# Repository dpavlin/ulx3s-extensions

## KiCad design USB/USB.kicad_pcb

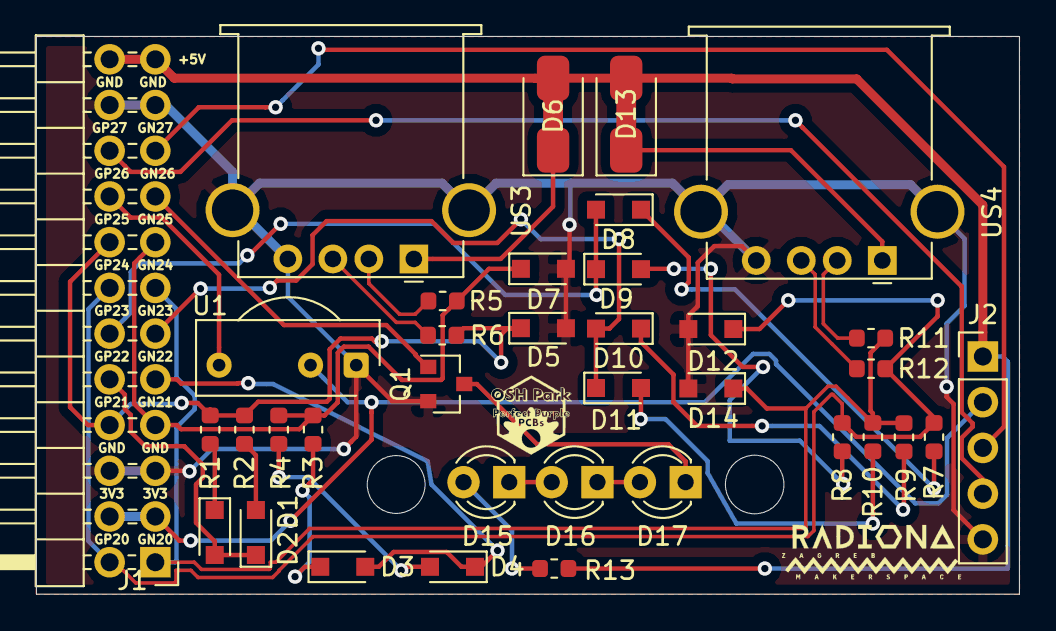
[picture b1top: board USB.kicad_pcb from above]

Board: 2 copper layers, 54.6 x 31.0 mm, 36 parts (0 on the bottom side), 33 nets.

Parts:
D1, D2, D3, D4, D8, D9, D10, D11: 1N914; D_SOD-323_HandSoldering
D5, D7, D12, D14: 3.6V; D_SOD-323_HandSoldering
D6, D13: 0; D_SMA_Jumper_NC
D15, D16, D17: LED; LED_D3.0mm_IRBlack
J1: Conn_02x12_Odd_Even; PinHeader_2x12_P2.54mm_Horizontal
J2: CONN; PinHeader_1x05_P2.54mm_Vertical
Q1: 2N7002; SOT-23
R1, R3, R7, R9: 1.1k; R_0603_1608Metric
R2, R4, R8, R10: 15k; R_0603_1608Metric
R5, R6, R11, R12, R13: 27; R_0603_1608Metric
U1: TSOP17xx; Vishay_CAST-3Pin
US3, US4: USB_A; USB_A_Stewart_SS-52100-001_Horizontal

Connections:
+3V3: J1.3, J1.4, J2.2, U1.2
+5V: D6.2, D13.2, J1.23, J1.24, J2.1, R13.1
/FPD1+: R6.2, US3.3
/FPD1-: R5.2, US3.2
/FPD2+: R12.2, US4.3
/FPD2-: R11.2, US4.2
/US1VBUS: D6.1, US3.1
/US2VBUS: D13.1, US4.1
GN26: J1.17, Q1.1
GN27: J1.19, J2.3
GND: D5.2, D7.2, D12.2, D14.2, J1.5, J1.6, J1.21, J1.22, J2.5, Q1.2, U1.1, US3.4, US3.5, US4.4, US4.5
GP26: J1.18, U1.3
GP27: J1.20, J2.4
unnamed: D1.1, R1.1
unnamed: D2.2, R2.1
unnamed: D3.1, R3.2
unnamed: D4.2, R4.1
unnamed: D8.1, R7.1
unnamed: D9.2, R8.1
unnamed: D10.1, R9.2
unnamed: D11.2, R10.1
unnamed: D15.1, D16.2
unnamed: D15.2, R13.2
unnamed: D16.1, D17.2
unnamed: D17.1, Q1.3
USB1_FPGA_D+: D5.1, J1.8, J1.16, R1.2, R2.2, R6.1
USB1_FPGA_D-: D7.1, J1.7, J1.15, R3.1, R4.2, R5.1
USB1_FPGA_PULL_D+: D1.2, D2.1, J1.10
USB1_FPGA_PULL_D-: D3.2, D4.1, J1.9
USB2_FPGA_D+: D12.1, J1.2, J1.14, R7.2, R8.2, R12.1
USB2_FPGA_D-: D14.1, J1.1, J1.13, R9.1, R10.2, R11.1
USB2_FPGA_PULL_D+: D8.2, D9.1, J1.12
USB2_FPGA_PULL_D-: D10.2, D11.1, J1.11

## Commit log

2021-07-23 update to host pcbnew 5.99.0+really5.1.10+dfsg1-1
2021-07-23 added background silkscreen J2 connector pins
